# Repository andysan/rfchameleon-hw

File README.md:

<!--
SPDX-FileCopyrightText: Copyright 2023 Andreas Sandberg <andreas@sandberg.uk>

SPDX-License-Identifier: Apache-2.0
-->

# What is RF Chameleon

RF Chameleon is a set of tools to interface with ISM-band radios. It's
inspired by [RFQuack](https://rfquack.org/) but provides a more
abstract interface to the radio which implies that it needs to make
more assumptions about the underlying protocol. Unlike RFQuack, RF
Chameleon is not intended as an RF exploration tool. RF Chameleon is
intended to be used in the phase after basic exploration when the
underlying radio parameters are known.

This repository contains custom boards that have been designed
specifically for RF Chameleon.

# Firmware

See the
[rfchameleon-fw](https://github.com/rfchameleon/rfchameleon-fw)
project for more details.

# Boards

## RF Chameleon CC1101

This board is based on an STM32F401 and a [eByte
E07](https://www.cdebyte.com/products/E07-900MM10S) module containing
a [Texas Instruments CC1101](https://www.ti.com/product/CC1101) radio.

Early revisions of this board was known as the *RF McQuack CC1101*.

**Warning:** Revision 1 of this board has several known hardware
   defects that require patching before the board can be used.

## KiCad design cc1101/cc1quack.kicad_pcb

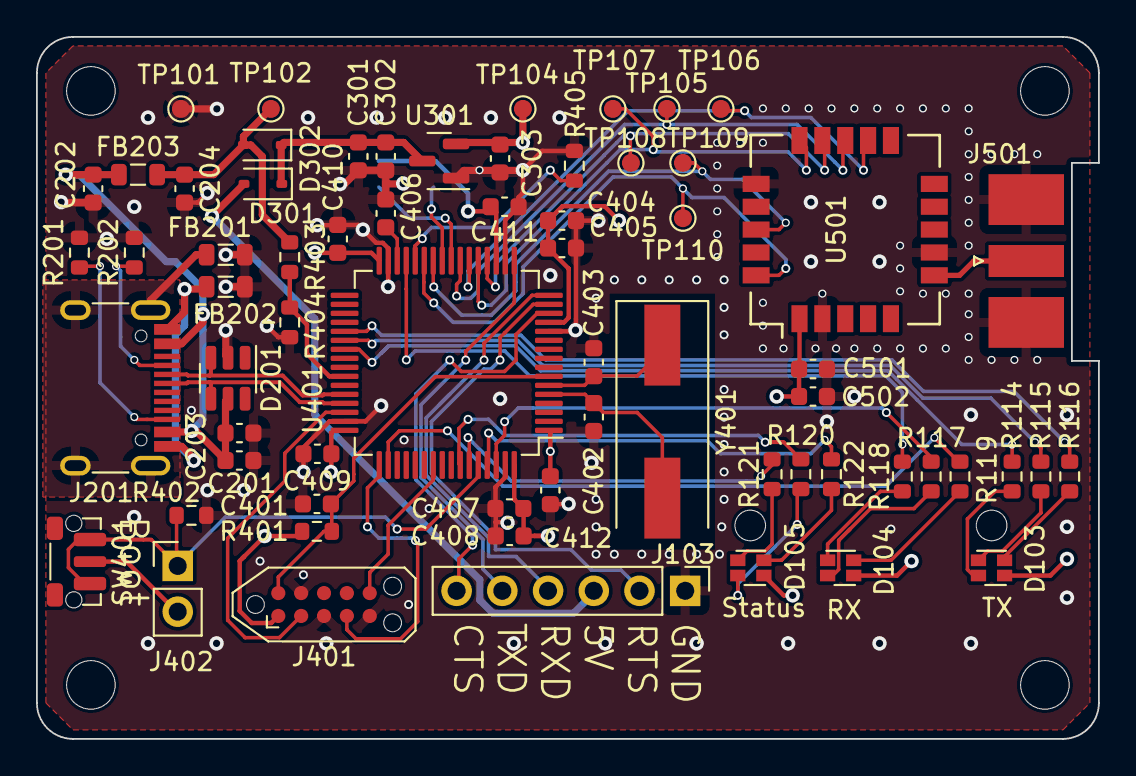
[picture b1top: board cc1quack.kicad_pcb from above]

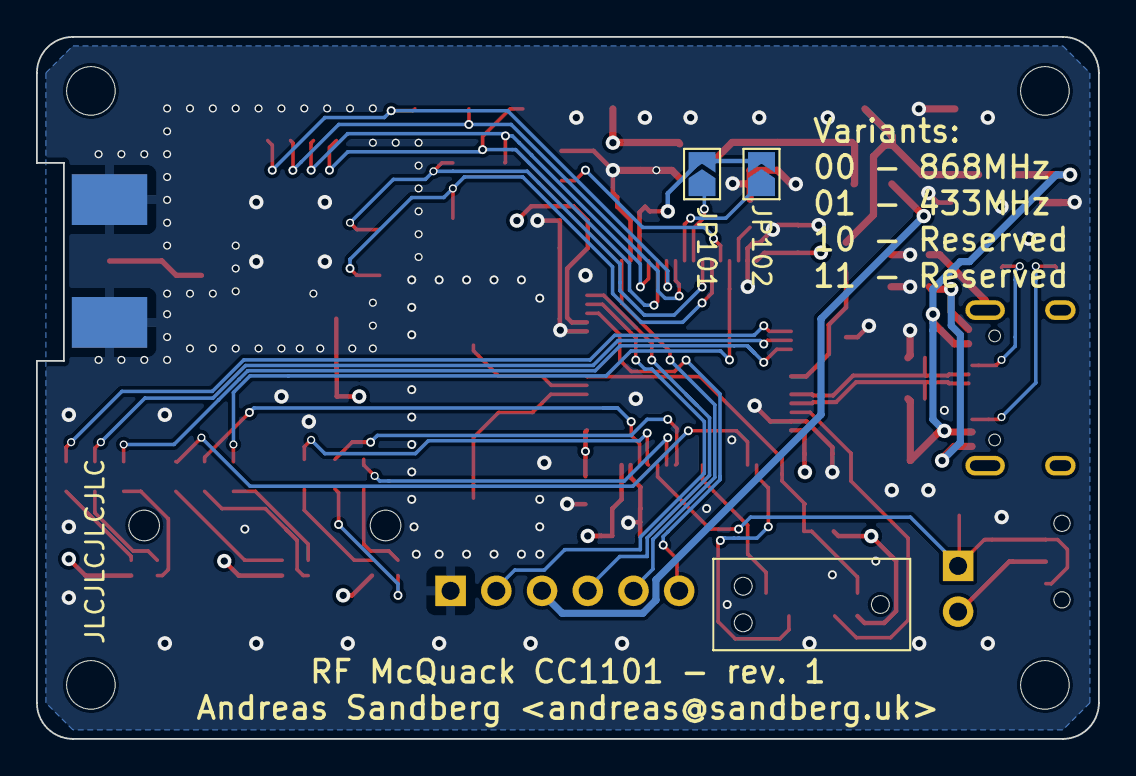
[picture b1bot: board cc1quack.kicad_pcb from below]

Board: 4 copper layers, 59.0 x 39.0 mm, 71 parts (2 on the bottom side), 53 nets.

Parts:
C201: DNP; C_0603_1608Metric
C202: 10nF; C_0603_1608Metric
C203, C204, C401, C405, C407, C409, C410, C411, C412, C501: 100nF; C_0603_1608Metric
C301, C408: 4.7uF; C_0603_1608Metric
C302, C303, C502: 1uF; C_0603_1608Metric
C402, C403: 20pF C0G; C_0603_1608Metric
C404: 1.0uF; C_0603_1608Metric
C406: 2.2uF X5R; C_0603_1608Metric
D103, D104, D105: LED; LED_LiteOn_LTST-C19HE1WT
D201: SRV05-4; SOT-23-6
D301, D302: 1N5819WS; D_SOD-323
FB201, FB202, FB203: 120R/0.5A; L_0805_2012Metric
H101, H102, H103, H104: MountingHole_Pad; MountingHole_2.7mm_M2.5
J103: Conn_01x06_Pin; PinHeader_1x06_P2.54mm_Vertical
J201: USB_C_Receptacle; USB_C_Receptacle_HRO_TYPE-C-31-M-12
J401: Conn_ARM_JTAG_SWD_10; Tag-Connect_TC2050-IDC-NL_2x05_P1.27mm_Vertical_with_bottom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
J402: Conn_01x02; PinHeader_1x02_P2.54mm_Vertical
J501: Conn_Coaxial; SMA_Molex_73251-2120_EdgeMount_Horizontal
JP101, JP102: SolderJumper_2_Open; SolderJumper-2_P1.3mm_Open_TrianglePad1.0x1.5mm
R114, R117, R120: 150R; R_0603_1608Metric
R115, R116, R118, R119, R121, R122: 47R; R_0603_1608Metric
R201, R202: 5k1, 20%; R_0603_1608Metric
R401, R402, R405: 10k; R_0603_1608Metric
R403: 82k; R_0603_1608Metric
R404: 33k; R_0603_1608Metric
SW401: Alps SKRTLAE010; SW_Push_1P1T-MP_NO_Horizontal_Alps_SKRTLAE010
TP101, TP102, TP104, TP105, TP106, TP107, TP108, TP109, TP110: TestPoint; TestPoint_Pad_D1.0mm
U301: XC6206P332MR; SOT-23
U401: STM32F401RCT6; LQFP-64_10x10mm_P0.5mm
U501: Ebyte-E07-900MM10S; Ebyte E07-400MM10S
Y401: 8MHz 20pF; Crystal_SMD_HC49-SD

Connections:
/EXT_5V: D301.2 (A), J103.3
/LED_RX_B: R119.2, U401.50 (PA15)
/LED_RX_G: R118.2, U401.29 (PB10)
/LED_RX_R: R117.2, U401.62 (PB9)
/LED_STATUS_B: R122.2, U401.61 (PB8)
/LED_STATUS_G: R121.2, U401.59 (PB7)
/LED_STATUS_R: R120.2, U401.58 (PB6)
/LED_TX_B: R116.2, U401.37 (PC6)
/LED_TX_G: R115.2, U401.38 (PC7)
/LED_TX_R: R114.2, U401.39 (PC8)
/MCU/BOOT0: J402.1, R402.1, SW401.1 (A), U401.60 (BOOT0)
/MCU/BOOT1: R405.2, U401.28 (PB2)
/MCU/OSC_IN: C402.1, U401.5 (PH0), Y401.2
/MCU/OSC_OUT: C403.1, U401.6 (PH1), Y401.1
/MCU/RF_GDO0: TP109.1, U401.26 (PB0), U501.18 (GDO0)
/MCU/RF_GDO2: TP110.1, U401.27 (PB1), U501.20 (GDO2)
/MCU/SPI_CLK: TP107.1, U401.21 (PA5), U501.15 (SCK)
/MCU/SPI_MISO: TP106.1, U401.22 (PA6), U501.12 (MISO/GDO1)
/MCU/SPI_MOSI: TP105.1, U401.23 (PA7), U501.13 (MOSI)
/MCU/SWCLK: J401.4 (SWDCLK/TCK), U401.49 (PA14)
/MCU/SWDIO: J401.2 (SWDIO/TMS), U401.46 (PA13)
/MCU/SWO: J401.6 (SWO/TDO), U401.55 (PB3)
/MCU/USB_D+: D201.4 (IO3), J201.A6 (D+), J201.B6 (D+), U401.45 (PA12)
/MCU/USB_D-: D201.3 (IO2), J201.A7 (D-), J201.B7 (D-), U401.44 (PA11)
/MCU/USB_VBUS: C204.1, D302.2 (A), FB203.2, R403.1, TP102.1
/MCU/USB_VBUS_SENSE: R403.2, R404.1, U401.42 (PA9)
/MCU/~RF_CS: TP108.1, U401.20 (PA4), U501.14 (~CS)
/MCU/~RST: C401.2, J401.10 (~RESET), R401.2, U401.7 (NRST)
/Radio/Ant: J501.1 (In), U501.6 (ANT)
/UART_RXD: J103.4, U401.16 (PA2)
/UART_TXD: J103.5, U401.17 (PA3)
/USB/USB_CC1: J201.A5 (CC1), R202.1
/USB/USB_CC2: J201.B5 (CC2), R201.1
/USB/USB_GND: FB202.1, J201.A1 (GND), J201.A12 (GND), J201.B1 (GND), J201.B12 (GND)
/USB/USB_SHIELD: FB201.1, J201.S1 (SHIELD)
/USB/VBUS_UF: C201.1, C202.1, C203.1, D201.5 (VP), FB203.1, J201.A4 (VBUS), J201.A9 (VBUS), J201.B4 (VBUS), J201.B9 (VBUS)
/VARIANT0: JP102.1 (A), U401.24 (PC4)
/VARIANT1: JP101.1 (A), U401.25 (PC5)
/~UART_CTS: J103.6, U401.14 (PA0)
/~UART_RTS: J103.2, U401.15 (PA1)
GND: C201.2, C202.2, C203.2, C204.2, C301.2, C302.2, C303.2, C401.1, C402.2, C403.2, C404.1, C405.1, C406.1, C407.1, C408.1, C409.2, C410.2, C411.2, C412.2, C501.1, C502.2, D201.2 (VN), FB201.2, FB202.2, J103.1, J401.3 (GND), J401.5 (GND), J401.9 (GNDDetect), J501.2 (Ext), R201.2, R202.2, R402.2, R404.2, R405.1, TP101.1, U301.1 (GND), U401.12 (VSSA), U401.18 (VSS), U401.31 (VSS), U401.47 (VSS), U401.63 (VSS), U501.2 (GND), U501.7 (GND), U501.16 (GND)
unnamed: D103.3 (BK), R116.1
unnamed: D103.2 (GK), R115.1
unnamed: D103.1 (RK), R114.1
unnamed: D104.3 (BK), R119.1
unnamed: D104.2 (GK), R118.1
unnamed: D104.1 (RK), R117.1
unnamed: D105.3 (BK), R122.1
unnamed: D105.2 (GK), R121.1
unnamed: D105.1 (RK), R120.1
unnamed: C301.1, C302.1, D301.1 (K), D302.1 (K), U301.3 (VI)
unnamed: C406.2, U401.30 (VCAP1)
VCC: C303.1, C404.2, C405.2, C407.2, C408.2, C409.1, C410.1, C411.1, C412.1, C501.2, C502.1, D103.4 (A), D104.4 (A), D105.4 (A), J401.1 (VTref), J402.2, JP101.2 (B), JP102.2 (B), R401.1, SW401.2 (B), TP104.1, U301.2 (VO), U401.1 (VBAT), U401.13 (VREF+), U401.19 (VDD), U401.32 (VDD), U401.48 (VDD), U401.64 (VDD), U501.1 (VCC)

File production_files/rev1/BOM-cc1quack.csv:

Comment,Designator,Footprint,LCSC
120R/0.5A,"FB201,FB202,FB203",L_0805_2012Metric,C1015
Alps SKRTLAE010,SW401,SW_Push_1P1T-MP_NO_Horizontal_Alps_SKRTLAE010,C110293
8MHz 20pF,Y401,Crystal_SMD_HC49-SD,C12674
100nF,"C203,C204,C401,C405,C407,C409,C410,C411,C412,C501",C_0603_1608Metric,C14663
1uF,"C302,C303,C404,C502",C_0603_1608Metric,C15849
20pF C0G,"C402,C403",C_0603_1608Metric,C1648
USB_C_Receptacle,J201,USB_C_Receptacle_HRO_TYPE-C-31-M-12,C165948
1N5819WS,"D301,D302",D_SOD-323,C191023
4.7uF,"C301,C408",C_0603_1608Metric,C19666
150R,"R114,R117,R120",R_0603_1608Metric,C22808
47R,"R115,R116,R118,R119,R121,R122",R_0603_1608Metric,C23182
"5k1, 20%","R201,R202",R_0603_1608Metric,C23186
82k,R403,R_0603_1608Metric,C23254
2.2uF X5R,C406,C_0603_1608Metric,C23630
10k,"R401,R402,R405",R_0603_1608Metric,C25804
33k,R404,R_0603_1608Metric,C4216
LED,"D103,D104,D105",LED_LiteOn_LTST-C19HE1WT,C458749
XC6206P332MR,U301,SOT-23,C5446
10nF,C202,C_0603_1608Metric,C57112
SRV05-4,D201,SOT-23-6,C7420376
STM32F401RCT6,U401,LQFP-64_10x10mm_P0.5mm,C74524

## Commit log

2024-01-22 Initialize repository
2024-01-22 Add RF McQuack CC1101 rev 1 schematics and PCB
2024-01-22 Add revision 1 production files
    Add production files used for revision one of the CC1101-based PCB.
2024-01-22 cc1quack: Add specialized switch footprint
    Specialize the ALPS SKRTLAE010 to include project-specific 3D model
    paths.
2024-01-22 cc1quack: Include both WRL and STP model paths
2024-01-22 cc1quack: Add 3D models README
2024-01-22 cc1quack: Specialize LiteOn LTST C19HE1WT footprint
    Specialize LiteOn LTST C19HE1WT footprint to include 3D models.
2024-01-22 Add a README.md
